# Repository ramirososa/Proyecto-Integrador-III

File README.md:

# Proyecto-Integrador-III
Proyecto Integrador III - Manuel Navarrete, Ignacio Olazabal, Ramiro Sosa

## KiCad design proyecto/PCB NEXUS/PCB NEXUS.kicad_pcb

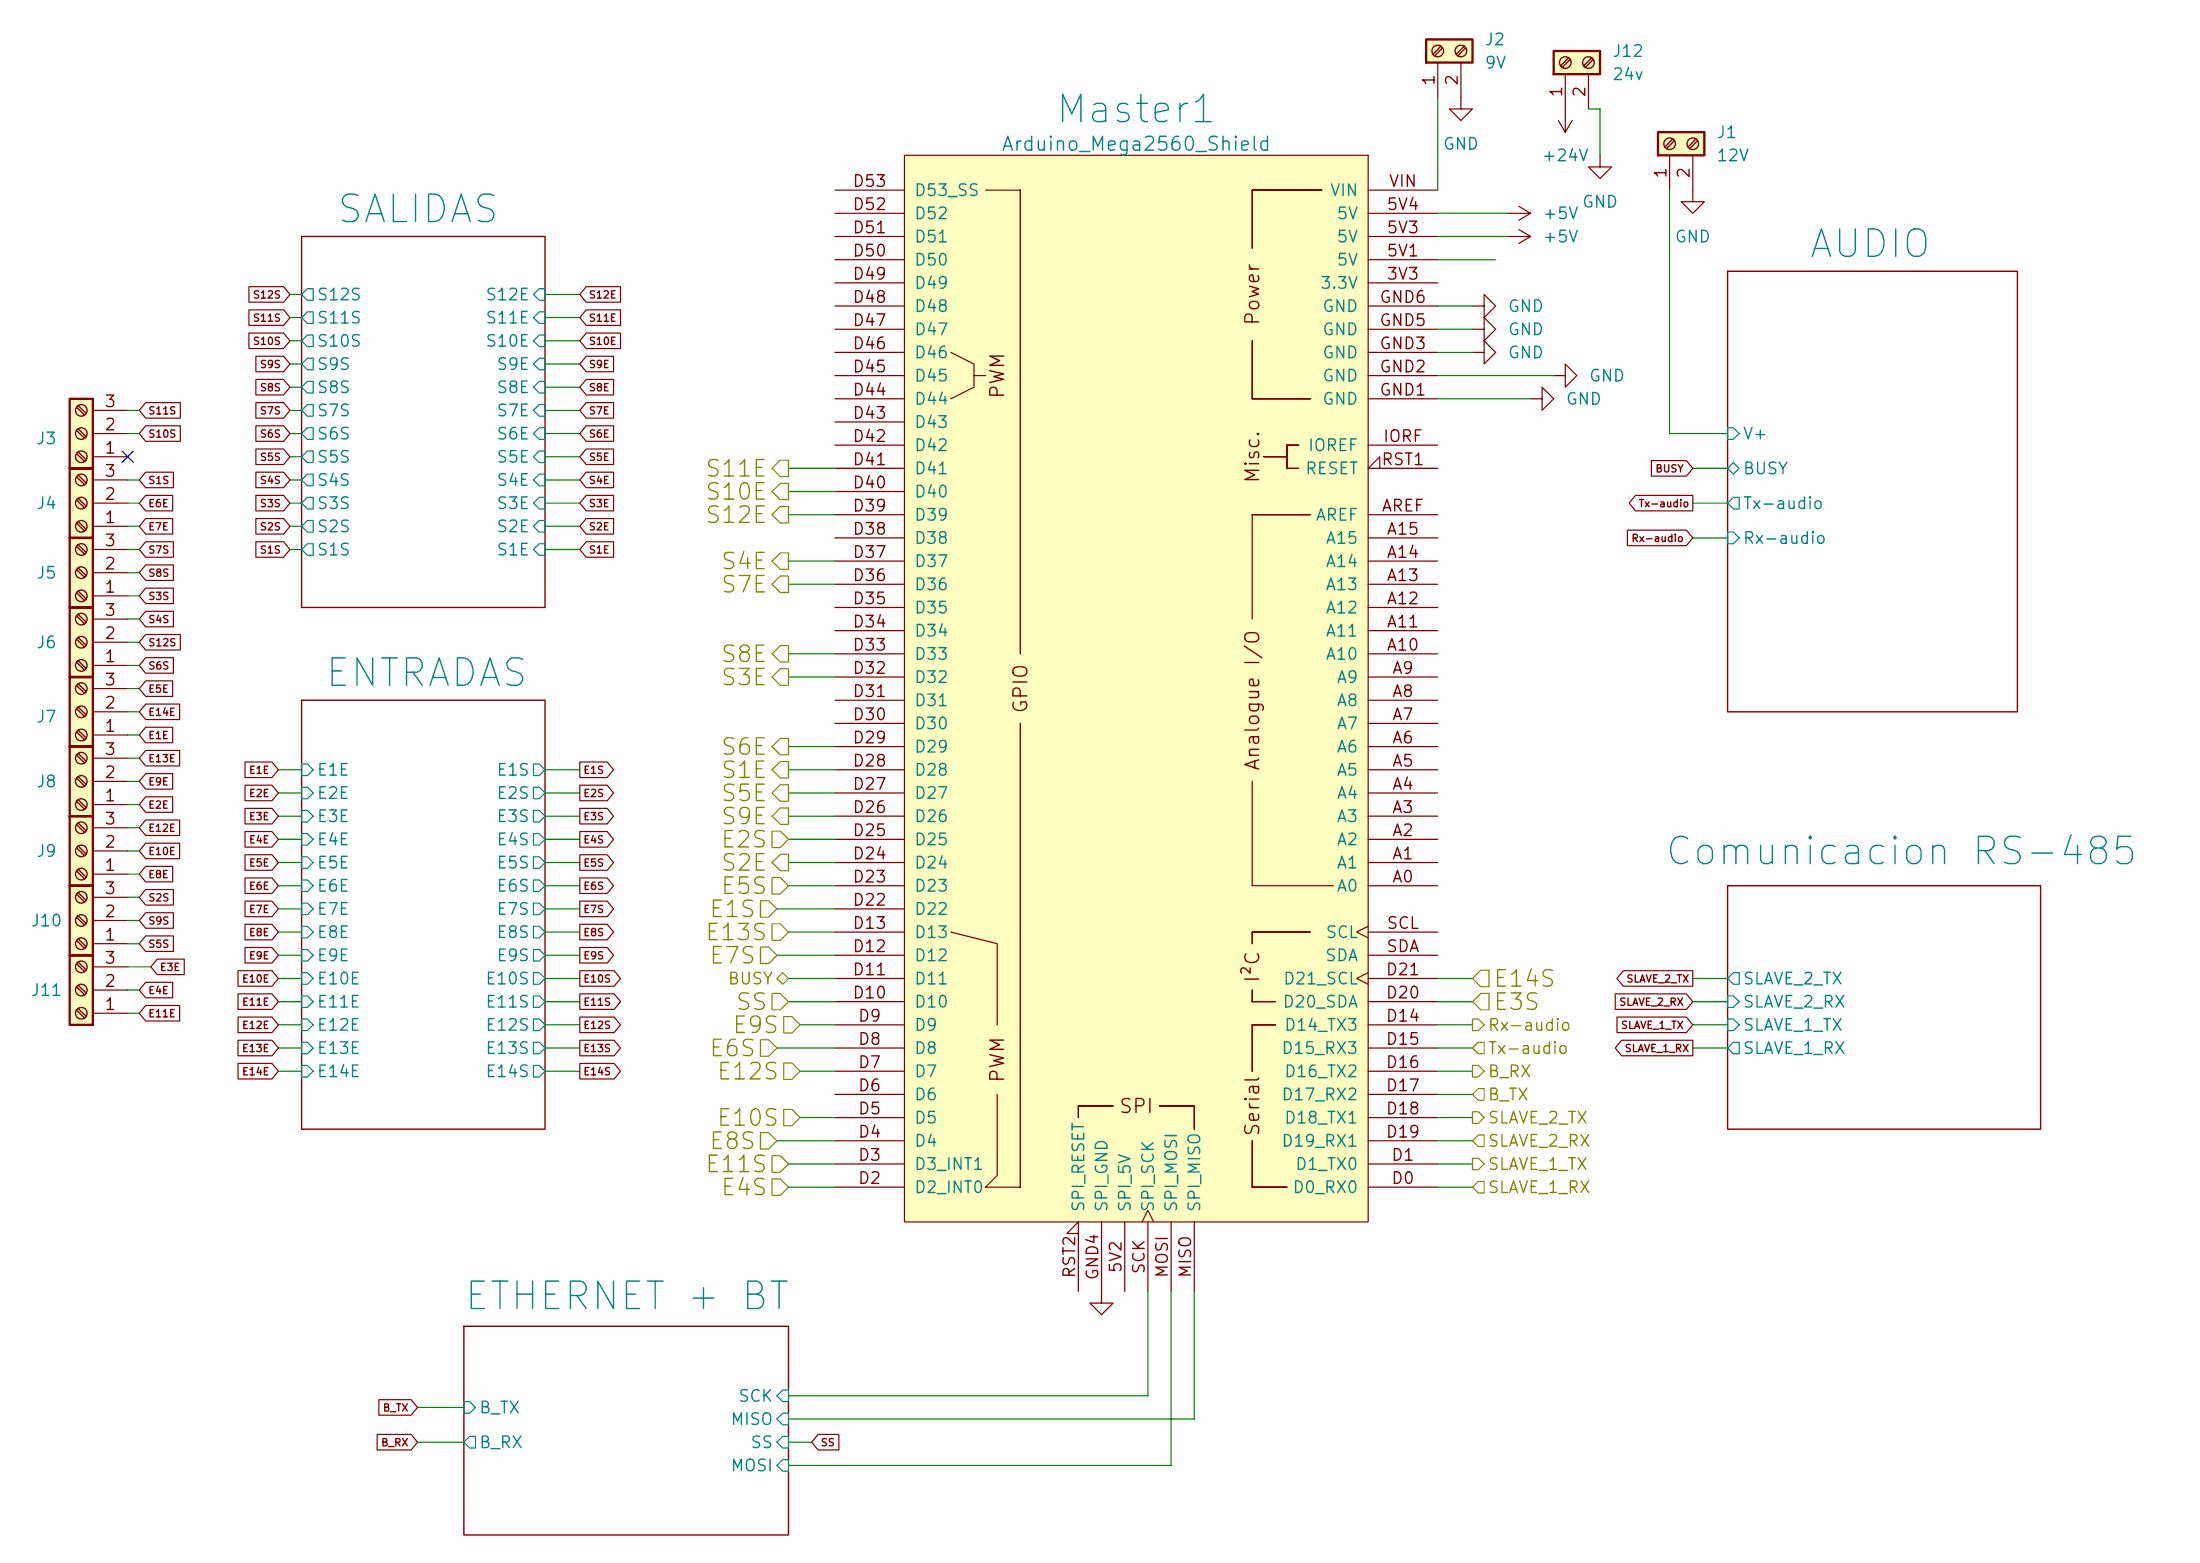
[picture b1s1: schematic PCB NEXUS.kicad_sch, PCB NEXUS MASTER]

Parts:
J1: 12V; TerminalBlock_bornier-2_P5.08mm
J2: 9V; TerminalBlock_bornier-2_P5.08mm
J3, J4, J5, J6, J7, J8, J9, J10, J11: Screw_Terminal_01x03; TerminalBlock_4Ucon_1x03_P3.50mm_Horizontal
J12: 24v; TerminalBlock_bornier-2_P5.08mm
Master1: Arduino_Mega2560_Shield

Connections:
+5V: Master1.5V3 (5V), Master1.5V4 (5V); also elsewhere on the board
+24V: J12.1; also elsewhere on the board
/AUDIO/V+: J1.1; also elsewhere on the board
/ETHERNET + BT/MISO: Master1.MISO (SPI_MISO); also elsewhere on the board
/ETHERNET + BT/MOSI: Master1.MOSI (SPI_MOSI); also elsewhere on the board
/ETHERNET + BT/SCK: Master1.SCK (SPI_SCK); also elsewhere on the board
BUSY: Master1.D11; also elsewhere on the board
B_RX: Master1.D16 (D16_TX2); also elsewhere on the board
B_TX: Master1.D17 (D17_RX2); also elsewhere on the board
E1E: J7.1; also elsewhere on the board
E1S: Master1.D22; also elsewhere on the board
E2E: J8.1; also elsewhere on the board
E2S: Master1.D25; also elsewhere on the board
E3E: J11.3; also elsewhere on the board
E3S: Master1.D20 (D20_SDA); also elsewhere on the board
E4E: J11.2; also elsewhere on the board
E4S: Master1.D2 (D2_INT0); also elsewhere on the board
E5E: J7.3; also elsewhere on the board
E5S: Master1.D23; also elsewhere on the board
E6E: J4.2; also elsewhere on the board
E6S: Master1.D8; also elsewhere on the board
E7E: J4.1; also elsewhere on the board
E7S: Master1.D12; also elsewhere on the board
E8E: J9.1; also elsewhere on the board
E8S: Master1.D4; also elsewhere on the board
E9E: J8.2; also elsewhere on the board
E9S: Master1.D9; also elsewhere on the board
E10E: J9.2; also elsewhere on the board
E10S: Master1.D5; also elsewhere on the board
E11E: J11.1; also elsewhere on the board
E11S: Master1.D3 (D3_INT1); also elsewhere on the board
E12E: J9.3; also elsewhere on the board
E12S: Master1.D7; also elsewhere on the board
E13E: J8.3; also elsewhere on the board
E13S: Master1.D13; also elsewhere on the board
E14E: J7.2; also elsewhere on the board
E14S: Master1.D21 (D21_SCL); also elsewhere on the board
GND: J1.2, J2.2, J12.2, Master1.GND1 (GND), Master1.GND2 (GND), Master1.GND3 (GND), Master1.GND4 (SPI_GND), Master1.GND5 (GND), Master1.GND6 (GND); also elsewhere on the board
unnamed: J2.1, Master1.VIN
Rx-audio: Master1.D14 (D14_TX3); also elsewhere on the board
S1E: Master1.D28; also elsewhere on the board
S1S: J4.3; also elsewhere on the board
S2E: Master1.D24; also elsewhere on the board
S2S: J10.3; also elsewhere on the board
S3E: Master1.D32; also elsewhere on the board
S3S: J5.1; also elsewhere on the board
S4E: Master1.D37; also elsewhere on the board
S4S: J6.3; also elsewhere on the board
S5E: Master1.D27; also elsewhere on the board
S5S: J10.1; also elsewhere on the board
S6E: Master1.D29; also elsewhere on the board
S6S: J6.1; also elsewhere on the board
S7E: Master1.D36; also elsewhere on the board
S7S: J5.3; also elsewhere on the board
S8E: Master1.D33; also elsewhere on the board
S8S: J5.2; also elsewhere on the board
S9E: Master1.D26; also elsewhere on the board
S9S: J10.2; also elsewhere on the board
S10E: Master1.D40; also elsewhere on the board
S10S: J3.2; also elsewhere on the board
S11E: Master1.D41; also elsewhere on the board
S11S: J3.3; also elsewhere on the board
S12E: Master1.D39; also elsewhere on the board
S12S: J6.2; also elsewhere on the board
SLAVE_1_RX: Master1.D0 (D0_RX0); also elsewhere on the board
SLAVE_1_TX: Master1.D1 (D1_TX0); also elsewhere on the board
SLAVE_2_RX: Master1.D19 (D19_RX1); also elsewhere on the board
SLAVE_2_TX: Master1.D18 (D18_TX1); also elsewhere on the board
SS: Master1.D10; also elsewhere on the board
Tx-audio: Master1.D15 (D15_RX3); also elsewhere on the board

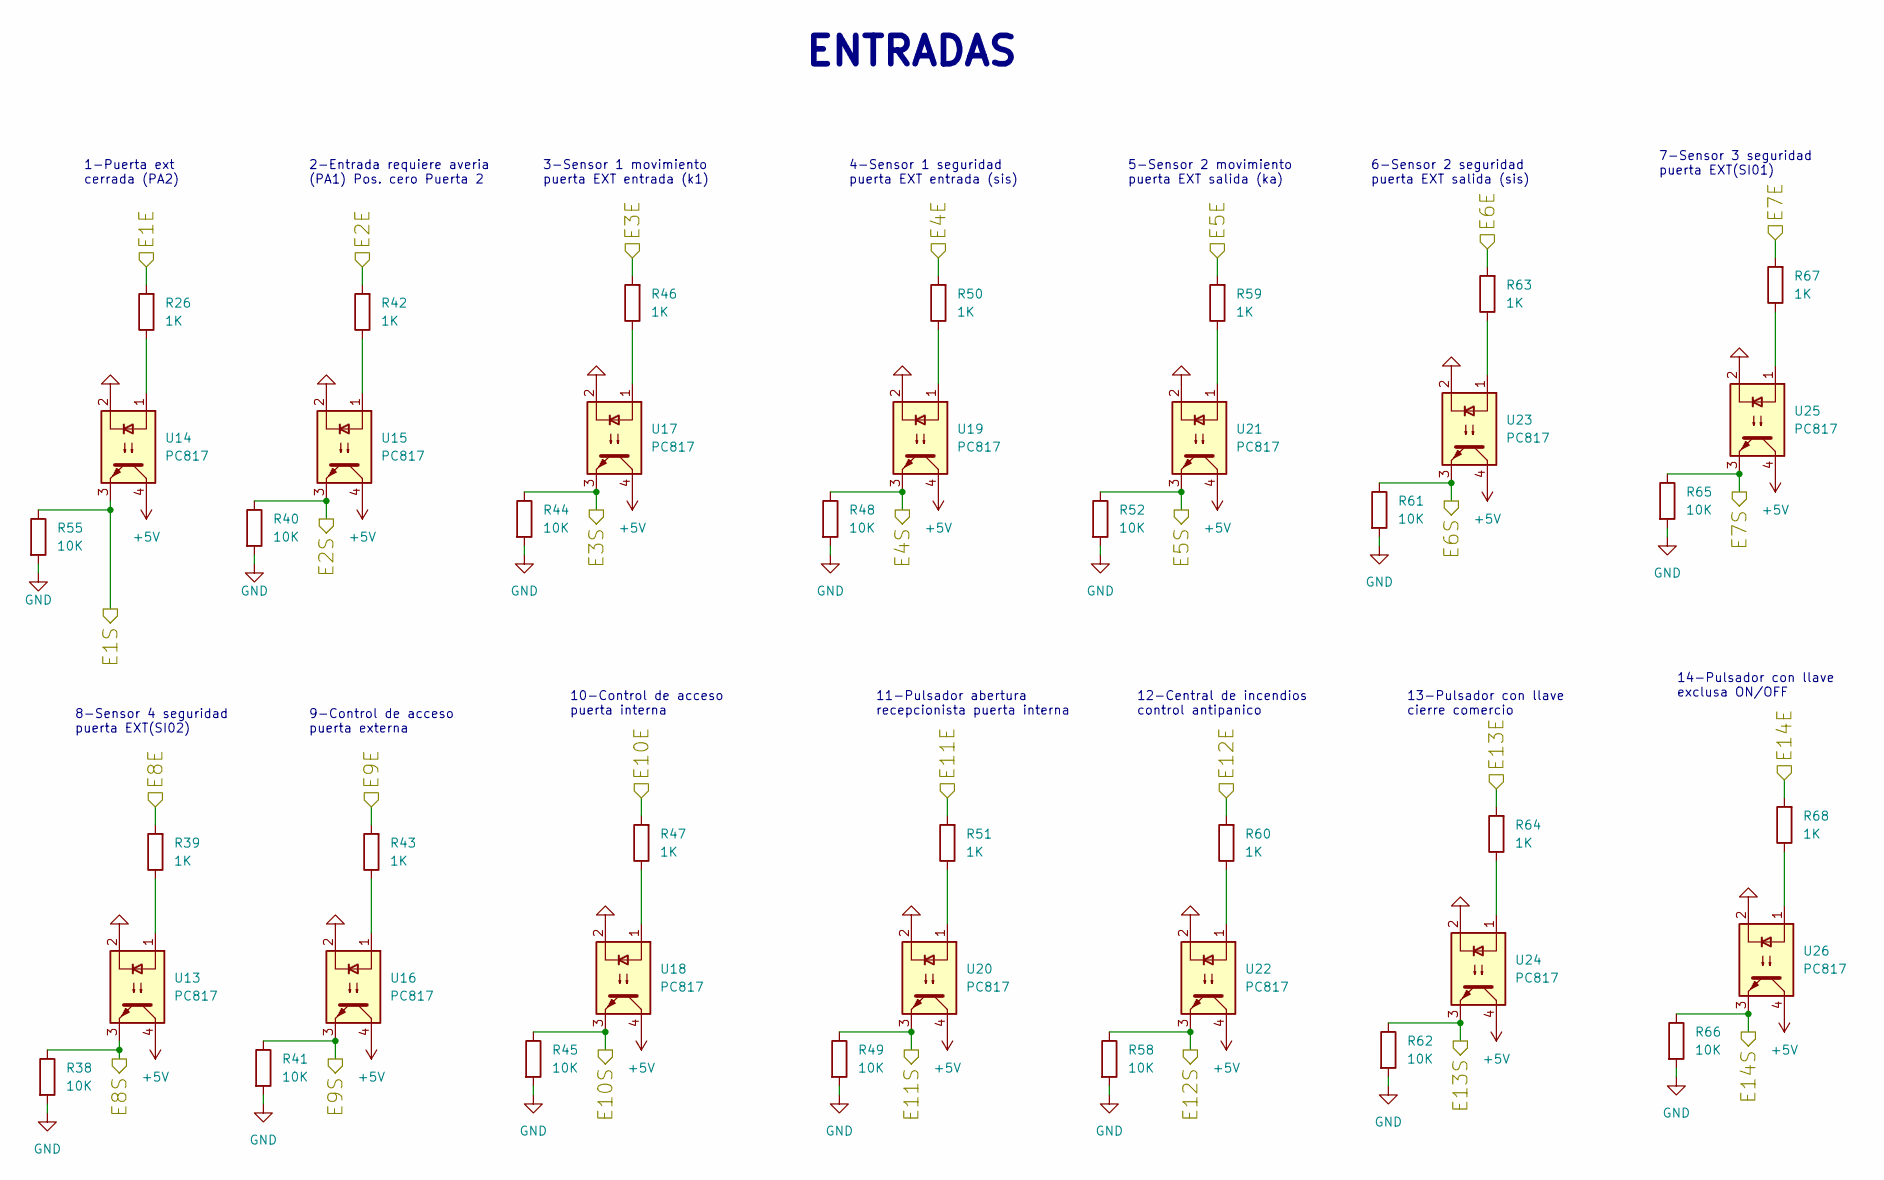
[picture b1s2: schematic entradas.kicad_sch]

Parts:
R26, R39, R42, R43, R46, R47, R50, R51, R59, R60, R63, R64, R67, R68: 1K; R_0805_2012Metric_Pad1.20x1.40mm_HandSolder
R38, R40, R41, R44, R45, R48, R49, R52, R55, R58, R61, R62, R65, R66: 10K; R_0805_2012Metric_Pad1.20x1.40mm_HandSolder
U13, U14, U15, U16, U17, U18, U19, U20, U21, U22, U23, U24, U25, U26: PC817; DIP-4_W7.62mm

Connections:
+5V: U13.4, U14.4, U15.4, U16.4, U17.4, U18.4, U19.4, U20.4, U21.4, U22.4, U23.4, U24.4, U25.4, U26.4; also elsewhere on the board
E1E: R26.2; also elsewhere on the board
E1S: R55.1, U14.3; also elsewhere on the board
E2E: R42.2; also elsewhere on the board
E2S: R40.1, U15.3; also elsewhere on the board
E3E: R46.2; also elsewhere on the board
E3S: R44.1, U17.3; also elsewhere on the board
E4E: R50.2; also elsewhere on the board
E4S: R48.1, U19.3; also elsewhere on the board
E5E: R59.2; also elsewhere on the board
E5S: R52.1, U21.3; also elsewhere on the board
E6E: R63.2; also elsewhere on the board
E6S: R61.1, U23.3; also elsewhere on the board
E7E: R67.2; also elsewhere on the board
E7S: R65.1, U25.3; also elsewhere on the board
E8E: R39.2; also elsewhere on the board
E8S: R38.1, U13.3; also elsewhere on the board
E9E: R43.2; also elsewhere on the board
E9S: R41.1, U16.3; also elsewhere on the board
E10E: R47.2; also elsewhere on the board
E10S: R45.1, U18.3; also elsewhere on the board
E11E: R51.2; also elsewhere on the board
E11S: R49.1, U20.3; also elsewhere on the board
E12E: R60.2; also elsewhere on the board
E12S: R58.1, U22.3; also elsewhere on the board
E13E: R64.2; also elsewhere on the board
E13S: R62.1, U24.3; also elsewhere on the board
E14E: R68.2; also elsewhere on the board
E14S: R66.1, U26.3; also elsewhere on the board
GND: R38.2, R40.2, R41.2, R44.2, R45.2, R48.2, R49.2, R52.2, R55.2, R58.2, R61.2, R62.2, R65.2, R66.2, U13.2, U14.2, U15.2, U16.2, U17.2, U18.2, U19.2, U20.2, U21.2, U22.2, U23.2, U24.2, U25.2, U26.2; also elsewhere on the board
unnamed: R26.1, U14.1
unnamed: R39.1, U13.1
unnamed: R42.1, U15.1
unnamed: R43.1, U16.1
unnamed: R46.1, U17.1
unnamed: R47.1, U18.1
unnamed: R50.1, U19.1
unnamed: R51.1, U20.1
unnamed: R59.1, U21.1
unnamed: R60.1, U22.1
unnamed: R63.1, U23.1
unnamed: R64.1, U24.1
unnamed: R67.1, U25.1
unnamed: R68.1, U26.1

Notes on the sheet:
4-Sensor 1 seguridad puerta EXT entrada (sis)
11-Pulsador abertura recepcionista puerta interna
9-Control de acceso puerta externa
14-Pulsador con llave exclusa ON/OFF
3-Sensor 1 movimiento puerta EXT entrada (k1)
1-Puerta ext cerrada (PA2)
12-Central de incendios control antipanico
13-Pulsador con llave cierre comercio
8-Sensor 4 seguridad puerta EXT(SI02)
7-Sensor 3 seguridad puerta EXT(SI01)
6-Sensor 2 seguridad puerta EXT salida (sis)
ENTRADAS
2-Entrada requiere averia (PA1) Pos. cero Puerta 2
10-Control de acceso puerta interna
5-Sensor 2 movimiento puerta EXT salida (ka)

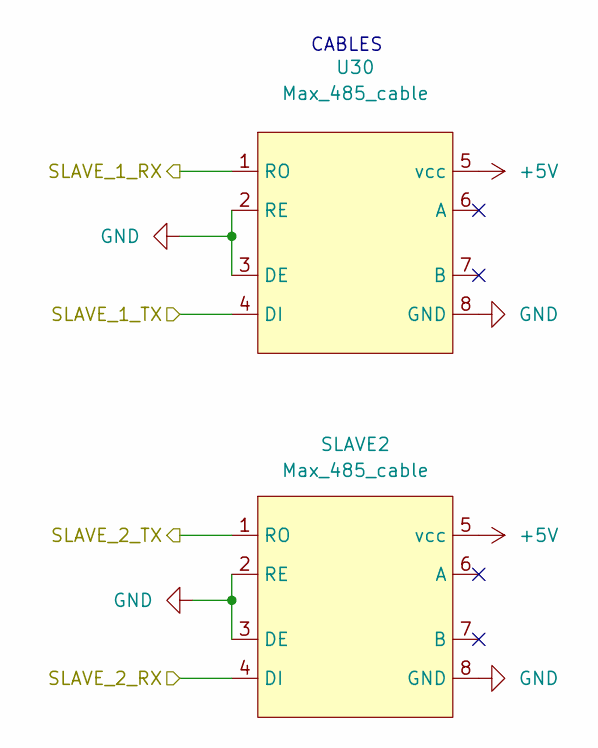
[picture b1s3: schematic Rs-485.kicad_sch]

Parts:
SLAVE2: Max_485_cable; modulo comuni 485
U30: Max_485_cable; modulo comuni 485

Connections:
+5V: SLAVE2.5 (vcc), U30.5 (vcc); also elsewhere on the board
GND: SLAVE2.2 (RE), SLAVE2.3 (DE), SLAVE2.8 (GND), U30.2 (RE), U30.3 (DE), U30.8 (GND); also elsewhere on the board
SLAVE_2_RX: SLAVE2.4 (DI); also elsewhere on the board
SLAVE_2_TX: SLAVE2.1 (RO); also elsewhere on the board

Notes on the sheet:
CABLES

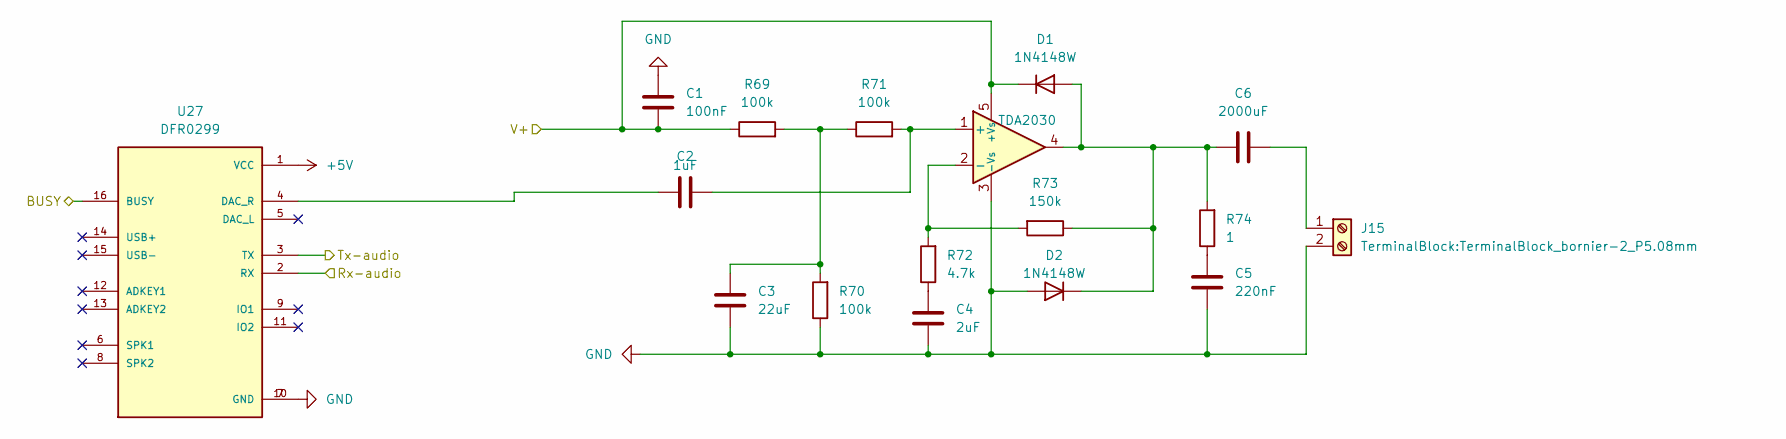
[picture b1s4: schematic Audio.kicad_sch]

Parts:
C1: 100nF; C_0805_2012Metric_Pad1.18x1.45mm_HandSolder
C2: 1uF; C_0805_2012Metric_Pad1.18x1.45mm_HandSolder
C3: 22uF; C_0805_2012Metric_Pad1.18x1.45mm_HandSolder
C4: 2uF; C_0805_2012Metric_Pad1.18x1.45mm_HandSolder
C5: 220nF; C_0805_2012Metric_Pad1.18x1.45mm_HandSolder
C6: 2000uF; C_0805_2012Metric_Pad1.18x1.45mm_HandSolder
D1, D2: 1N4148W; D_0805_2012Metric_Pad1.15x1.40mm_HandSolder
J15: TerminalBlock:TerminalBlock_bornier-2_P5.08mm; PHOENIX_1935161
R69, R70, R71: 100k; R_0805_2012Metric_Pad1.20x1.40mm_HandSolder
R72: 4.7k; R_0805_2012Metric_Pad1.20x1.40mm_HandSolder
R73: 150k; R_0805_2012Metric_Pad1.20x1.40mm_HandSolder
R74: 1; R_0805_2012Metric_Pad1.20x1.40mm_HandSolder
U27: DFR0299; MODULE_DFR0299
U28: TDA2030; TO-220-5_P3.4x3.7mm_StaggerOdd_Lead3.8mm_Vertical

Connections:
+5V: U27.1 (VCC); also elsewhere on the board
/AUDIO/V+: C1.2, D1.1 (K), R69.1, U28.5 (+Vs); also elsewhere on the board
BUSY: U27.16 (BUSY); also elsewhere on the board
GND: C1.1, C3.2, C4.2, C5.2, D2.2 (A), J15.2, R70.1, U27.7 (GND), U27.10 (GND), U28.3 (-Vs); also elsewhere on the board
unnamed: C2.1, U27.4 (DAC_R)
unnamed: C2.2, R71.2, U28.1 (+)
unnamed: C3.1, R69.2, R70.2, R71.1
unnamed: C4.1, R72.1
unnamed: C5.1, R74.1
unnamed: C6.1, J15.1
unnamed: C6.2, D1.2 (A), D2.1 (K), R73.1, R74.2, U28.4
unnamed: R72.2, R73.2, U28.2 (-)
Rx-audio: U27.2 (RX); also elsewhere on the board
Tx-audio: U27.3 (TX); also elsewhere on the board

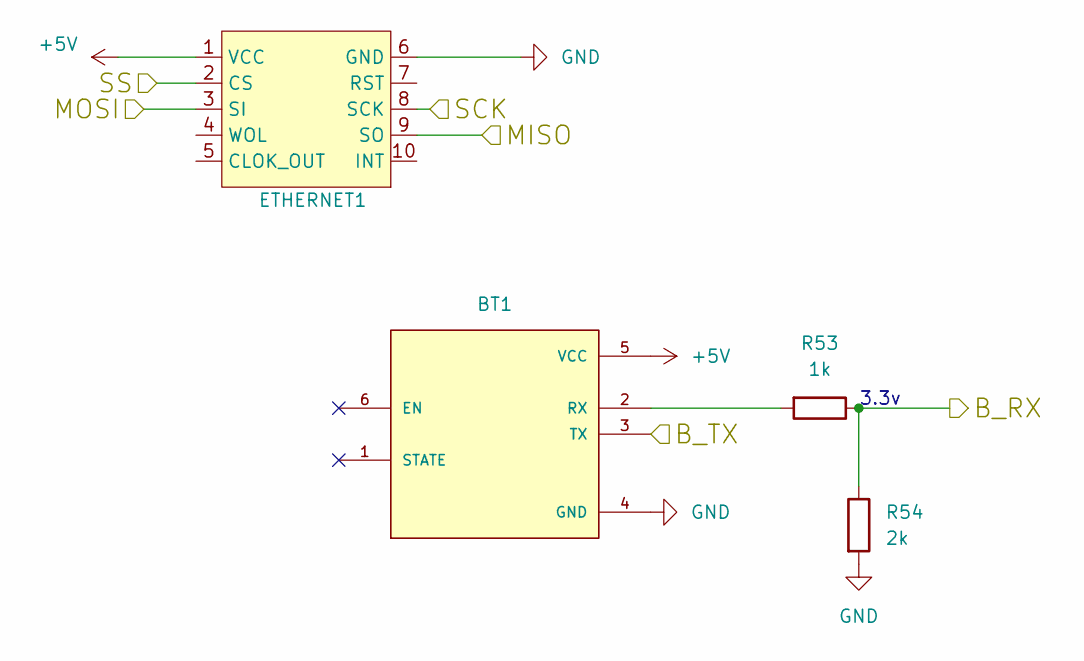
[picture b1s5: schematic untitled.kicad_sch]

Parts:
BT1: ZC142200; MODULE_ZC142200; PARTREV N/A
ETHERNET1: ENC28J60_NEXUS; ecnj
R53: 1k; R_0805_2012Metric_Pad1.20x1.40mm_HandSolder
R54: 2k; R_0805_2012Metric_Pad1.20x1.40mm_HandSolder

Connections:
+5V: BT1.5 (VCC), ETHERNET1.1 (VCC); also elsewhere on the board
/ETHERNET + BT/MISO: ETHERNET1.9 (SO); also elsewhere on the board
/ETHERNET + BT/MOSI: ETHERNET1.3 (SI); also elsewhere on the board
/ETHERNET + BT/SCK: ETHERNET1.8 (SCK); also elsewhere on the board
B_RX: R53.1, R54.1; also elsewhere on the board
B_TX: BT1.3 (TX); also elsewhere on the board
GND: BT1.4 (GND), ETHERNET1.6 (GND), R54.2; also elsewhere on the board
unnamed: BT1.2 (RX), R53.2
SS: ETHERNET1.2 (CS); also elsewhere on the board

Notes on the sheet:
3.3v

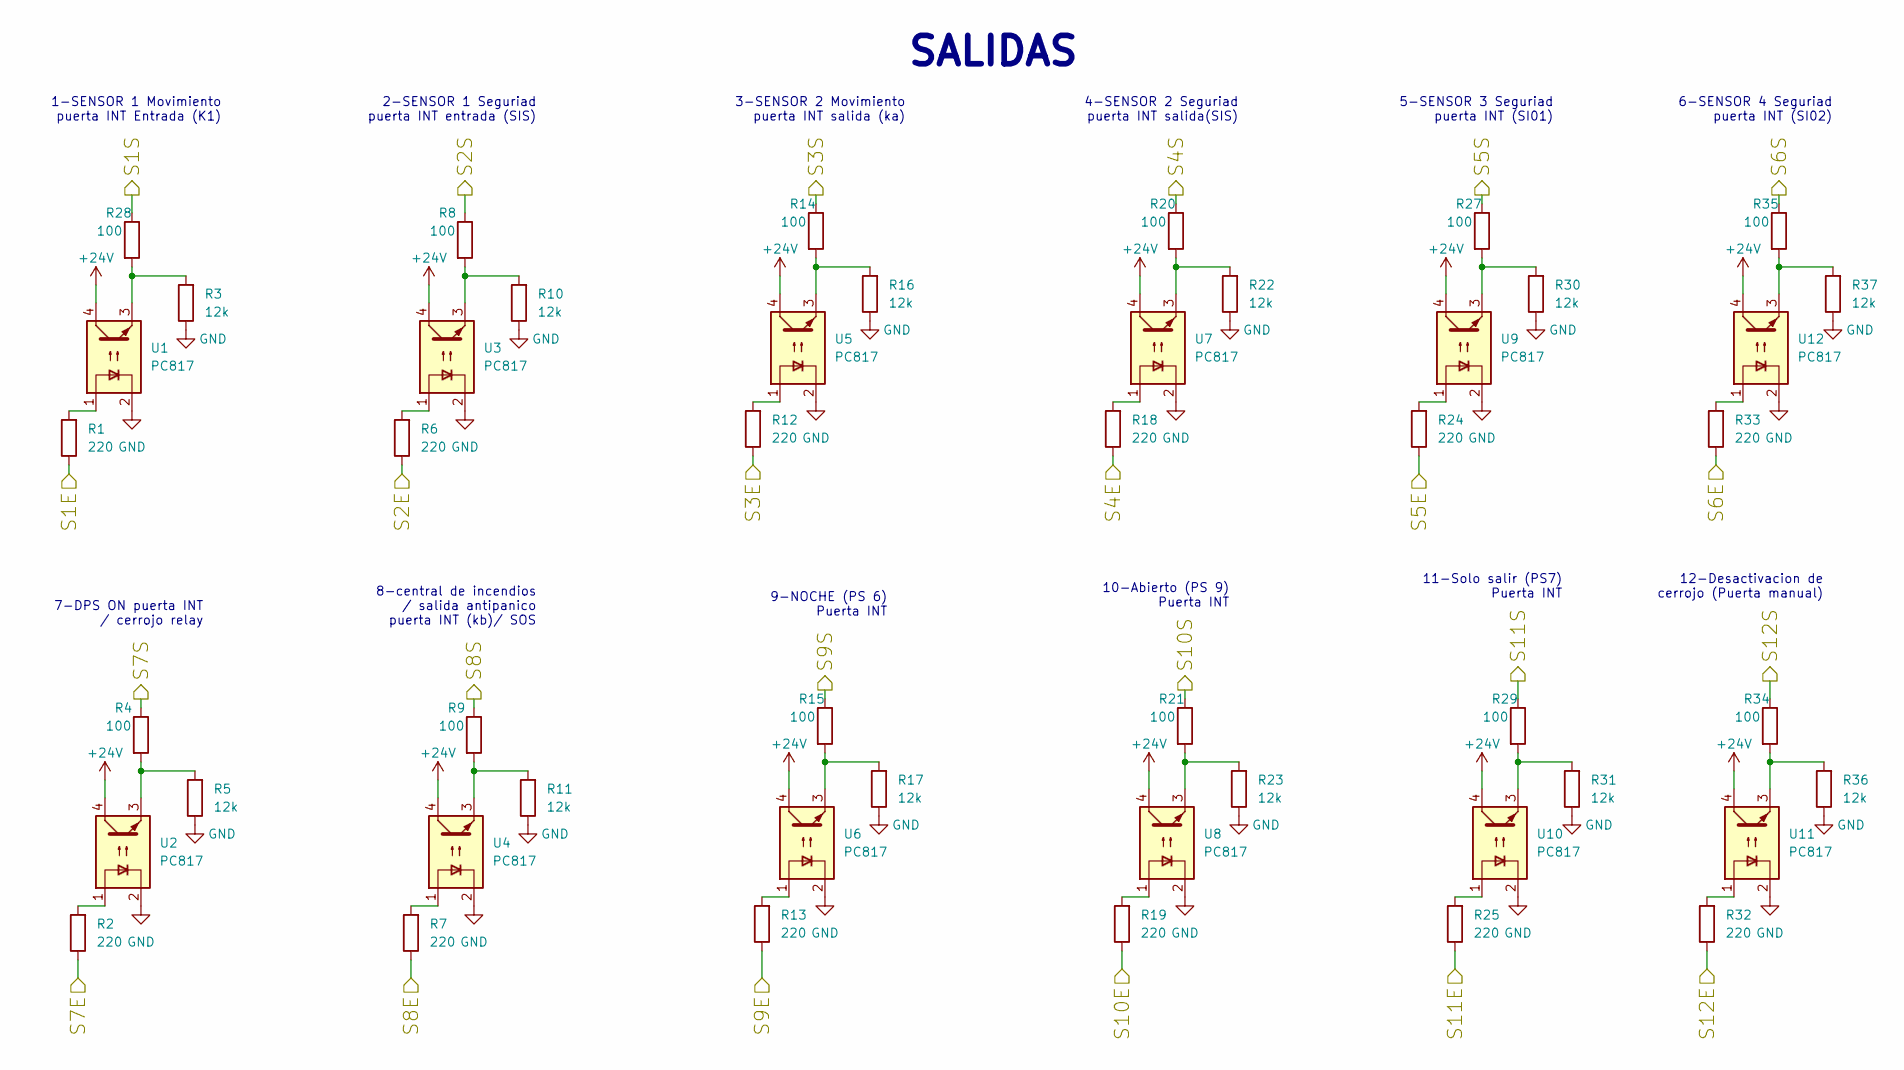
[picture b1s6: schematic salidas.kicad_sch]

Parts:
R1, R2, R6, R7, R12, R13, R18, R19, R24, R25, R32, R33: 220; R_0805_2012Metric_Pad1.20x1.40mm_HandSolder
R3, R5, R10, R11, R16, R17, R22, R23, R30, R31, R36, R37: 12k; R_0805_2012Metric_Pad1.20x1.40mm_HandSolder
R4, R8, R9, R14, R15, R20, R21, R27, R28, R29, R34, R35: 100; R_0805_2012Metric_Pad1.20x1.40mm_HandSolder
U1, U2, U3, U4, U5, U6, U7, U8, U9, U10, U11, U12: PC817; DIP-4_W7.62mm

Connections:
+24V: U1.4, U2.4, U3.4, U4.4, U5.4, U6.4, U7.4, U8.4, U9.4, U10.4, U11.4, U12.4; also elsewhere on the board
GND: R3.1, R5.1, R10.1, R11.1, R16.1, R17.1, R22.1, R23.1, R30.1, R31.1, R36.1, R37.1, U1.2, U2.2, U3.2, U4.2, U5.2, U6.2, U7.2, U8.2, U9.2, U10.2, U11.2, U12.2; also elsewhere on the board
unnamed: R1.2, U1.1
unnamed: R2.2, U2.1
unnamed: R4.2, R5.2, U2.3
unnamed: R6.2, U3.1
unnamed: R7.2, U4.1
unnamed: R8.2, R10.2, U3.3
unnamed: R9.2, R11.2, U4.3
unnamed: R12.2, U5.1
unnamed: R13.2, U6.1
unnamed: R14.2, R16.2, U5.3
unnamed: R15.2, R17.2, U6.3
unnamed: R18.2, U7.1
unnamed: R19.2, U8.1
unnamed: R20.2, R22.2, U7.3
unnamed: R21.2, R23.2, U8.3
unnamed: R24.2, U9.1
unnamed: R25.2, U10.1
unnamed: R27.2, R30.2, U9.3
unnamed: R3.2, R28.2, U1.3
unnamed: R29.2, R31.2, U10.3
unnamed: R32.2, U11.1
unnamed: R33.2, U12.1
unnamed: R34.2, R36.2, U11.3
unnamed: R35.2, R37.2, U12.3
S1E: R1.1; also elsewhere on the board
S1S: R28.1; also elsewhere on the board
S2E: R6.1; also elsewhere on the board
S2S: R8.1; also elsewhere on the board
S3E: R12.1; also elsewhere on the board
S3S: R14.1; also elsewhere on the board
S4E: R18.1; also elsewhere on the board
S4S: R20.1; also elsewhere on the board
S5E: R24.1; also elsewhere on the board
S5S: R27.1; also elsewhere on the board
S6E: R33.1; also elsewhere on the board
S6S: R35.1; also elsewhere on the board
S7E: R2.1; also elsewhere on the board
S7S: R4.1; also elsewhere on the board
S8E: R7.1; also elsewhere on the board
S8S: R9.1; also elsewhere on the board
S9E: R13.1; also elsewhere on the board
S9S: R15.1; also elsewhere on the board
S10E: R19.1; also elsewhere on the board
S10S: R21.1; also elsewhere on the board
S11E: R25.1; also elsewhere on the board
S11S: R29.1; also elsewhere on the board
S12E: R32.1; also elsewhere on the board
S12S: R34.1; also elsewhere on the board

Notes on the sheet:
9-NOCHE (PS 6) Puerta INT
SALIDAS
5-SENSOR 3 Seguriad puerta INT (SI01)
7-DPS ON puerta INT / cerrojo relay
8-central de incendios / salida antipanico puerta INT (kb)/ SOS
4-SENSOR 2 Seguriad puerta INT salida(SIS)
3-SENSOR 2 Movimiento puerta INT salida (ka)
11-Solo salir (PS7) Puerta INT
12-Desactivacion de cerrojo (Puerta manual)
2-SENSOR 1 Seguriad puerta INT entrada (SIS)
1-SENSOR 1 Movimiento puerta INT Entrada (K1)
6-SENSOR 4 Seguriad puerta INT (SI02)
10-Abierto (PS 9) Puerta INT

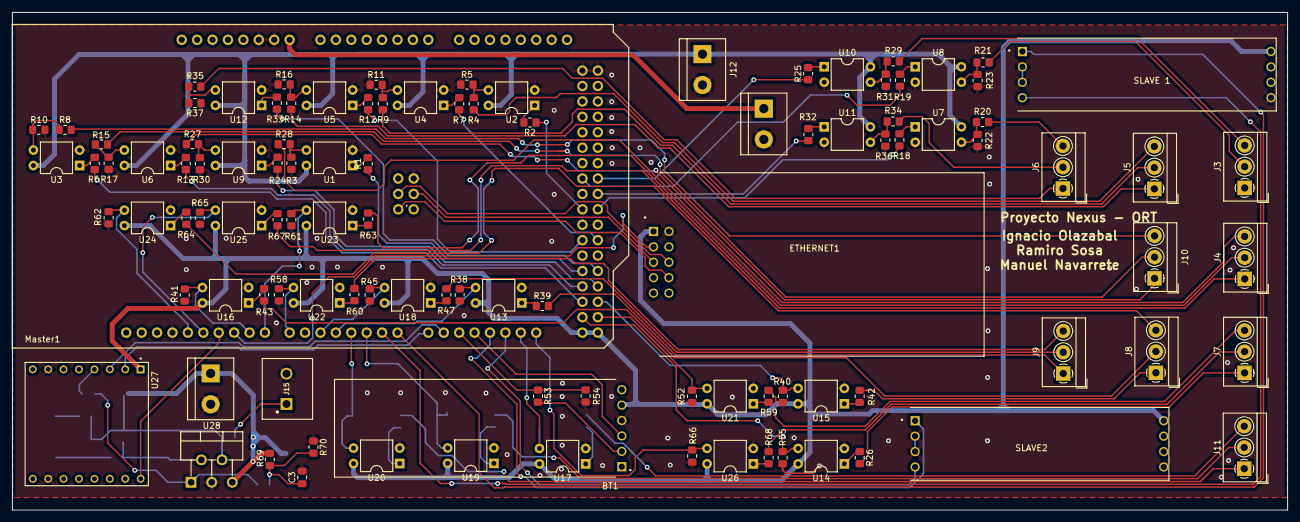
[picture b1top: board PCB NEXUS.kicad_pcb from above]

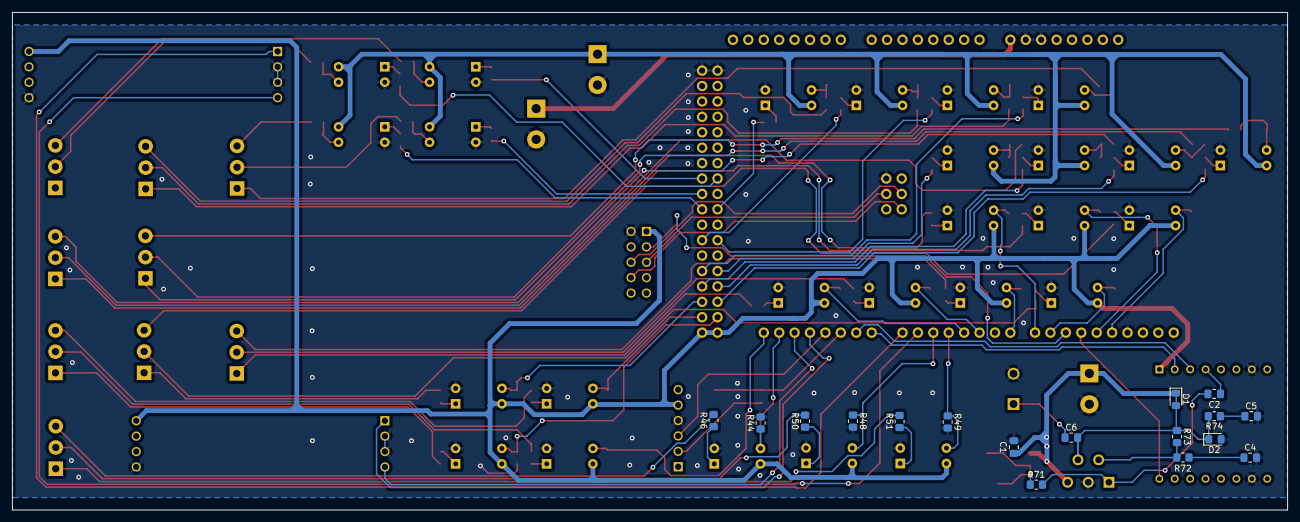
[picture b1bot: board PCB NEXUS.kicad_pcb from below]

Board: 2 copper layers, 210.1 x 82.0 mm, 126 parts (17 on the bottom side), 117 nets.

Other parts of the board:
SLAVE 1: Max_485_cable; modulo comuni 485

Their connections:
+5V: SLAVE 1.5 (vcc); also elsewhere on the board
GND: SLAVE 1.2 (RE), SLAVE 1.3 (DE), SLAVE 1.8 (GND); also elsewhere on the board
SLAVE_1_RX: SLAVE 1.1 (RO); also elsewhere on the board
SLAVE_1_TX: SLAVE 1.4 (DI); also elsewhere on the board

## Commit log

2022-10-01 Agregar interrupciones
    Agregamos carpeta de tests
2022-10-01 prueba hc-05 + serial_begin
2022-10-01 Created main & heading file
2022-10-08 Ultimo cambio HC-05
2022-10-11 setup interrupts 10/10
2022-10-11 comienzo estructura entradas 11/10
2022-10-18 Actualizacion 17/10
    Agregamos logica de entradas
2022-10-23 Reestructura pooling y logica
2022-10-28 Update logica del 27 oct
2022-10-31 Mejoras estructura main + codigo para probar leds
2022-11-01 Mejorar Estructura + tests RS485
2022-11-10 se bugeo
2022-11-22 Update 21 Nov
    Agrego modo noche, panico, solosalir. Mejoras Logica, cambio loop principal. Agregamos conexion eth..
2022-11-27 Version sin debug, falta integrar ETH y DFR
2022-11-28 y buenio..
2022-11-28 Update con Proyecto Leds
    La carpeta proyecto leds tiene el codigo con el cual hicimos los videos para validar el software a traves de leds e inputs seriales
2022-11-28 proyecto leds main
2022-11-29 Agregamos archivos kickad
2022-11-29 Subida del master Slave para PCB
2022-11-29 Fotos del proyecto
